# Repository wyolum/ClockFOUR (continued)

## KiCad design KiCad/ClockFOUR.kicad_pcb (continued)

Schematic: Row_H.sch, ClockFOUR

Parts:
C110, C111, C112, C113, C114, C115, C116, C117, C118, C119, C120, C121, C122, C123: 100n; c_0805
LED99, LED100, LED101, LED102, LED103, LED104, LED105, LED106, LED107, LED108, LED109, LED110, LED111, LED112: WS2812B

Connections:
5V: C110.2, C111.2, C112.2, C113.2, C114.2, C115.2, C116.2, C117.2, C118.2, C119.2, C120.2, C121.2, C122.2, C123.2, LED99.1 (VDD), LED100.1 (VDD), LED101.1 (VDD), LED102.1 (VDD), LED103.1 (VDD), LED104.1 (VDD), LED105.1 (VDD), LED106.1 (VDD), LED107.1 (VDD), LED108.1 (VDD), LED109.1 (VDD), LED110.1 (VDD), LED111.1 (VDD), LED112.1 (VDD); also elsewhere on the board
/Row_H/DI_H: LED99.4 (DI); also elsewhere on the board
/Row_I/DI_I: LED112.2 (DO); also elsewhere on the board
GND: C110.1, C111.1, C112.1, C113.1, C114.1, C115.1, C116.1, C117.1, C118.1, C119.1, C120.1, C121.1, C122.1, C123.1, LED99.3 (VSS), LED100.3 (VSS), LED101.3 (VSS), LED102.3 (VSS), LED103.3 (VSS), LED104.3 (VSS), LED105.3 (VSS), LED106.3 (VSS), LED107.3 (VSS), LED108.3 (VSS), LED109.3 (VSS), LED110.3 (VSS), LED111.3 (VSS), LED112.3 (VSS); also elsewhere on the board
unnamed: LED100.2 (DO), LED101.4 (DI)
unnamed: LED99.2 (DO), LED100.4 (DI)
unnamed: LED101.2 (DO), LED102.4 (DI)
unnamed: LED102.2 (DO), LED103.4 (DI)
unnamed: LED103.2 (DO), LED104.4 (DI)
unnamed: LED104.2 (DO), LED105.4 (DI)
unnamed: LED105.2 (DO), LED106.4 (DI)
unnamed: LED106.2 (DO), LED107.4 (DI)
unnamed: LED107.2 (DO), LED108.4 (DI)
unnamed: LED108.2 (DO), LED109.4 (DI)
unnamed: LED109.2 (DO), LED110.4 (DI)
unnamed: LED110.2 (DO), LED111.4 (DI)
unnamed: LED111.2 (DO), LED112.4 (DI)

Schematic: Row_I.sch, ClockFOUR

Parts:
C124, C125, C126, C127, C128, C129, C130, C131, C132, C133, C134, C135, C136, C137: 100n; c_0805
LED113, LED114, LED115, LED116, LED117, LED118, LED119, LED120, LED121, LED122, LED123, LED124, LED125, LED126: WS2812B

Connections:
5V: C124.2, C125.2, C126.2, C127.2, C128.2, C129.2, C130.2, C131.2, C132.2, C133.2, C134.2, C135.2, C136.2, C137.2, LED113.1 (VDD), LED114.1 (VDD), LED115.1 (VDD), LED116.1 (VDD), LED117.1 (VDD), LED118.1 (VDD), LED119.1 (VDD), LED120.1 (VDD), LED121.1 (VDD), LED122.1 (VDD), LED123.1 (VDD), LED124.1 (VDD), LED125.1 (VDD), LED126.1 (VDD); also elsewhere on the board
/Row_I/DI_I: LED113.4 (DI); also elsewhere on the board
/Row_J/DI_J: LED126.2 (DO); also elsewhere on the board
GND: C124.1, C125.1, C126.1, C127.1, C128.1, C129.1, C130.1, C131.1, C132.1, C133.1, C134.1, C135.1, C136.1, C137.1, LED113.3 (VSS), LED114.3 (VSS), LED115.3 (VSS), LED116.3 (VSS), LED117.3 (VSS), LED118.3 (VSS), LED119.3 (VSS), LED120.3 (VSS), LED121.3 (VSS), LED122.3 (VSS), LED123.3 (VSS), LED124.3 (VSS), LED125.3 (VSS), LED126.3 (VSS); also elsewhere on the board
unnamed: LED113.2 (DO), LED114.4 (DI)
unnamed: LED114.2 (DO), LED115.4 (DI)
unnamed: LED115.2 (DO), LED116.4 (DI)
unnamed: LED116.2 (DO), LED117.4 (DI)
unnamed: LED117.2 (DO), LED118.4 (DI)
unnamed: LED118.2 (DO), LED119.4 (DI)
unnamed: LED119.2 (DO), LED120.4 (DI)
unnamed: LED120.2 (DO), LED121.4 (DI)
unnamed: LED121.2 (DO), LED122.4 (DI)
unnamed: LED122.2 (DO), LED123.4 (DI)
unnamed: LED123.2 (DO), LED124.4 (DI)
unnamed: LED124.2 (DO), LED125.4 (DI)
unnamed: LED125.2 (DO), LED126.4 (DI)

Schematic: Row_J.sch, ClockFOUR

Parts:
C138, C139, C140, C141, C142, C143, C144, C145, C146, C147, C148, C149, C150, C151: 100n; c_0805
LED127, LED128, LED129, LED130, LED131, LED132, LED133, LED134, LED135, LED136, LED137, LED138, LED139, LED140: WS2812B; RGB_WS2811B

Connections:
5V: C138.2, C139.2, C140.2, C141.2, C142.2, C143.2, C144.2, C145.2, C146.2, C147.2, C148.2, C149.2, C150.2, C151.2, LED127.1 (VDD), LED128.1 (VDD), LED129.1 (VDD), LED130.1 (VDD), LED131.1 (VDD), LED132.1 (VDD), LED133.1 (VDD), LED134.1 (VDD), LED135.1 (VDD), LED136.1 (VDD), LED137.1 (VDD), LED138.1 (VDD), LED139.1 (VDD), LED140.1 (VDD); also elsewhere on the board
/Row_J/DI_J: LED127.4 (DI); also elsewhere on the board
/Row_K/DI_K: LED140.2 (DO); also elsewhere on the board
GND: C138.1, C139.1, C140.1, C141.1, C142.1, C143.1, C144.1, C145.1, C146.1, C147.1, C148.1, C149.1, C150.1, C151.1, LED127.3 (VSS), LED128.3 (VSS), LED129.3 (VSS), LED130.3 (VSS), LED131.3 (VSS), LED132.3 (VSS), LED133.3 (VSS), LED134.3 (VSS), LED135.3 (VSS), LED136.3 (VSS), LED137.3 (VSS), LED138.3 (VSS), LED139.3 (VSS), LED140.3 (VSS); also elsewhere on the board
unnamed: LED127.2 (DO), LED128.4 (DI)
unnamed: LED128.2 (DO), LED129.4 (DI)
unnamed: LED129.2 (DO), LED130.4 (DI)
unnamed: LED130.2 (DO), LED131.4 (DI)
unnamed: LED131.2 (DO), LED132.4 (DI)
unnamed: LED132.2 (DO), LED133.4 (DI)
unnamed: LED133.2 (DO), LED134.4 (DI)
unnamed: LED134.2 (DO), LED135.4 (DI)
unnamed: LED135.2 (DO), LED136.4 (DI)
unnamed: LED136.2 (DO), LED137.4 (DI)
unnamed: LED137.2 (DO), LED138.4 (DI)
unnamed: LED138.2 (DO), LED139.4 (DI)
unnamed: LED139.2 (DO), LED140.4 (DI)

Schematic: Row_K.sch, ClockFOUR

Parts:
C152, C153, C154, C155, C156, C157, C158, C159, C160, C161, C162, C163, C164, C165: 100n; c_0805
LED141, LED142, LED143, LED144, LED145, LED146, LED147, LED148, LED149, LED150, LED151, LED152, LED153, LED154: WS2812B

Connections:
5V: C152.2, C153.2, C154.2, C155.2, C156.2, C157.2, C158.2, C159.2, C160.2, C161.2, C162.2, C163.2, C164.2, C165.2, LED141.1 (VDD), LED142.1 (VDD), LED143.1 (VDD), LED144.1 (VDD), LED145.1 (VDD), LED146.1 (VDD), LED147.1 (VDD), LED148.1 (VDD), LED149.1 (VDD), LED150.1 (VDD), LED151.1 (VDD), LED152.1 (VDD), LED153.1 (VDD), LED154.1 (VDD); also elsewhere on the board
/Row_K/DI_K: LED141.4 (DI); also elsewhere on the board
/Row_L/DI_L: LED154.2 (DO); also elsewhere on the board
GND: C152.1, C153.1, C154.1, C155.1, C156.1, C157.1, C158.1, C159.1, C160.1, C161.1, C162.1, C163.1, C164.1, C165.1, LED141.3 (VSS), LED142.3 (VSS), LED143.3 (VSS), LED144.3 (VSS), LED145.3 (VSS), LED146.3 (VSS), LED147.3 (VSS), LED148.3 (VSS), LED149.3 (VSS), LED150.3 (VSS), LED151.3 (VSS), LED152.3 (VSS), LED153.3 (VSS), LED154.3 (VSS); also elsewhere on the board
unnamed: LED141.2 (DO), LED142.4 (DI)
unnamed: LED142.2 (DO), LED143.4 (DI)
unnamed: LED143.2 (DO), LED144.4 (DI)
unnamed: LED144.2 (DO), LED145.4 (DI)
unnamed: LED145.2 (DO), LED146.4 (DI)
unnamed: LED146.2 (DO), LED147.4 (DI)
unnamed: LED147.2 (DO), LED148.4 (DI)
unnamed: LED148.2 (DO), LED149.4 (DI)
unnamed: LED149.2 (DO), LED150.4 (DI)
unnamed: LED150.2 (DO), LED151.4 (DI)
unnamed: LED151.2 (DO), LED152.4 (DI)
unnamed: LED152.2 (DO), LED153.4 (DI)
unnamed: LED153.2 (DO), LED154.4 (DI)

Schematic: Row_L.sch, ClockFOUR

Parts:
C166, C167, C168, C169, C170, C171, C172, C173, C174, C175, C176, C177, C178, C179: 100n; c_0805
LED155, LED156, LED157, LED158, LED159, LED160, LED161, LED162, LED163, LED164, LED165, LED166, LED167, LED168: WS2812B

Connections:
5V: C166.2, C167.2, C168.2, C169.2, C170.2, C171.2, C172.2, C173.2, C174.2, C175.2, C176.2, C177.2, C178.2, C179.2, LED155.1 (VDD), LED156.1 (VDD), LED157.1 (VDD), LED158.1 (VDD), LED159.1 (VDD), LED160.1 (VDD), LED161.1 (VDD), LED162.1 (VDD), LED163.1 (VDD), LED164.1 (VDD), LED165.1 (VDD), LED166.1 (VDD), LED167.1 (VDD), LED168.1 (VDD); also elsewhere on the board
/Row_L/DI_L: LED155.4 (DI); also elsewhere on the board
/Row_M/DI_M: LED168.2 (DO); also elsewhere on the board
GND: C166.1, C167.1, C168.1, C169.1, C170.1, C171.1, C172.1, C173.1, C174.1, C175.1, C176.1, C177.1, C178.1, C179.1, LED155.3 (VSS), LED156.3 (VSS), LED157.3 (VSS), LED158.3 (VSS), LED159.3 (VSS), LED160.3 (VSS), LED161.3 (VSS), LED162.3 (VSS), LED163.3 (VSS), LED164.3 (VSS), LED165.3 (VSS), LED166.3 (VSS), LED167.3 (VSS), LED168.3 (VSS); also elsewhere on the board
unnamed: LED155.2 (DO), LED156.4 (DI)
unnamed: LED156.2 (DO), LED157.4 (DI)
unnamed: LED157.2 (DO), LED158.4 (DI)
unnamed: LED158.2 (DO), LED159.4 (DI)
unnamed: LED159.2 (DO), LED160.4 (DI)
unnamed: LED160.2 (DO), LED161.4 (DI)
unnamed: LED161.2 (DO), LED162.4 (DI)
unnamed: LED162.2 (DO), LED163.4 (DI)
unnamed: LED163.2 (DO), LED164.4 (DI)
unnamed: LED164.2 (DO), LED165.4 (DI)
unnamed: LED165.2 (DO), LED166.4 (DI)
unnamed: LED166.2 (DO), LED167.4 (DI)
unnamed: LED167.2 (DO), LED168.4 (DI)

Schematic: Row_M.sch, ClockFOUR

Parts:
C180, C181, C182, C183, C184, C185, C186, C187, C188, C189, C190, C191, C192, C193: 100n; c_0805
LED169, LED170, LED171, LED172, LED173, LED174, LED175, LED176, LED177, LED178, LED179, LED180, LED181, LED182: WS2812B; RGB_WS2811B

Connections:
5V: C180.2, C181.2, C182.2, C183.2, C184.2, C185.2, C186.2, C187.2, C188.2, C189.2, C190.2, C191.2, C192.2, C193.2, LED169.1 (VDD), LED170.1 (VDD), LED171.1 (VDD), LED172.1 (VDD), LED173.1 (VDD), LED174.1 (VDD), LED175.1 (VDD), LED176.1 (VDD), LED177.1 (VDD), LED178.1 (VDD), LED179.1 (VDD), LED180.1 (VDD), LED181.1 (VDD), LED182.1 (VDD); also elsewhere on the board
/Row_M/DI_M: LED169.4 (DI); also elsewhere on the board
/Row_M/DO_M: LED182.2 (DO)
GND: C180.1, C181.1, C182.1, C183.1, C184.1, C185.1, C186.1, C187.1, C188.1, C189.1, C190.1, C191.1, C192.1, C193.1, LED169.3 (VSS), LED170.3 (VSS), LED171.3 (VSS), LED172.3 (VSS), LED173.3 (VSS), LED174.3 (VSS), LED175.3 (VSS), LED176.3 (VSS), LED177.3 (VSS), LED178.3 (VSS), LED179.3 (VSS), LED180.3 (VSS), LED181.3 (VSS), LED182.3 (VSS); also elsewhere on the board
unnamed: LED169.2 (DO), LED170.4 (DI)
unnamed: LED170.2 (DO), LED171.4 (DI)
unnamed: LED171.2 (DO), LED172.4 (DI)
unnamed: LED172.2 (DO), LED173.4 (DI)
unnamed: LED173.2 (DO), LED174.4 (DI)
unnamed: LED174.2 (DO), LED175.4 (DI)
unnamed: LED175.2 (DO), LED176.4 (DI)
unnamed: LED176.2 (DO), LED177.4 (DI)
unnamed: LED177.2 (DO), LED178.4 (DI)
unnamed: LED178.2 (DO), LED179.4 (DI)
unnamed: LED179.2 (DO), LED180.4 (DI)
unnamed: LED180.2 (DO), LED181.4 (DI)
unnamed: LED181.2 (DO), LED182.4 (DI)

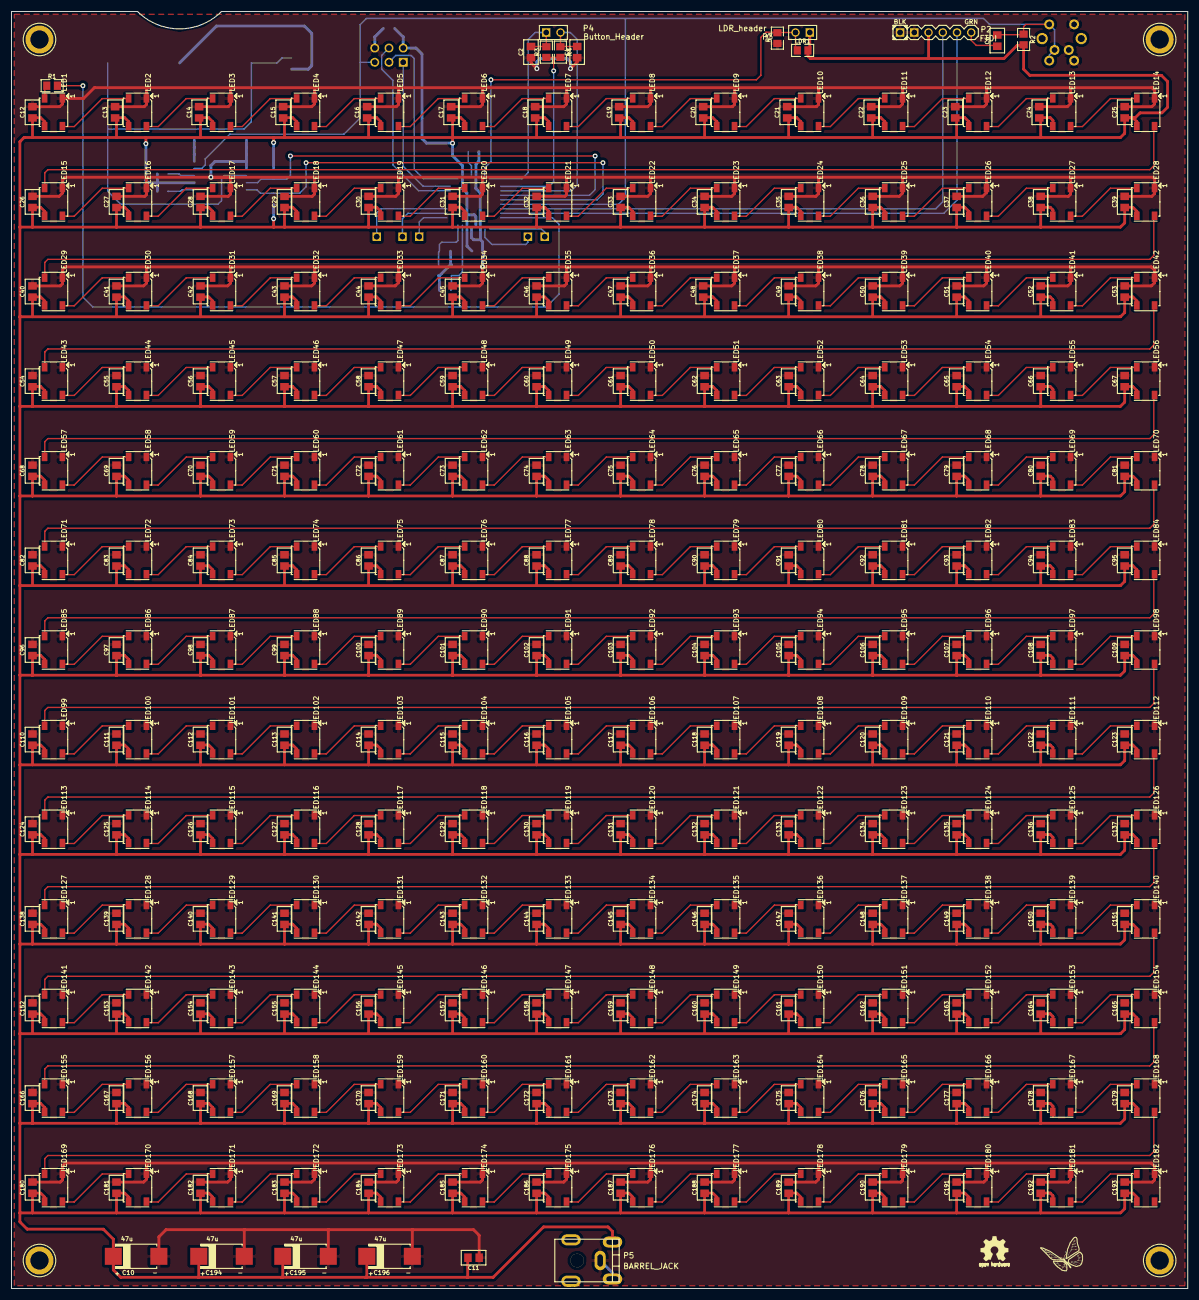
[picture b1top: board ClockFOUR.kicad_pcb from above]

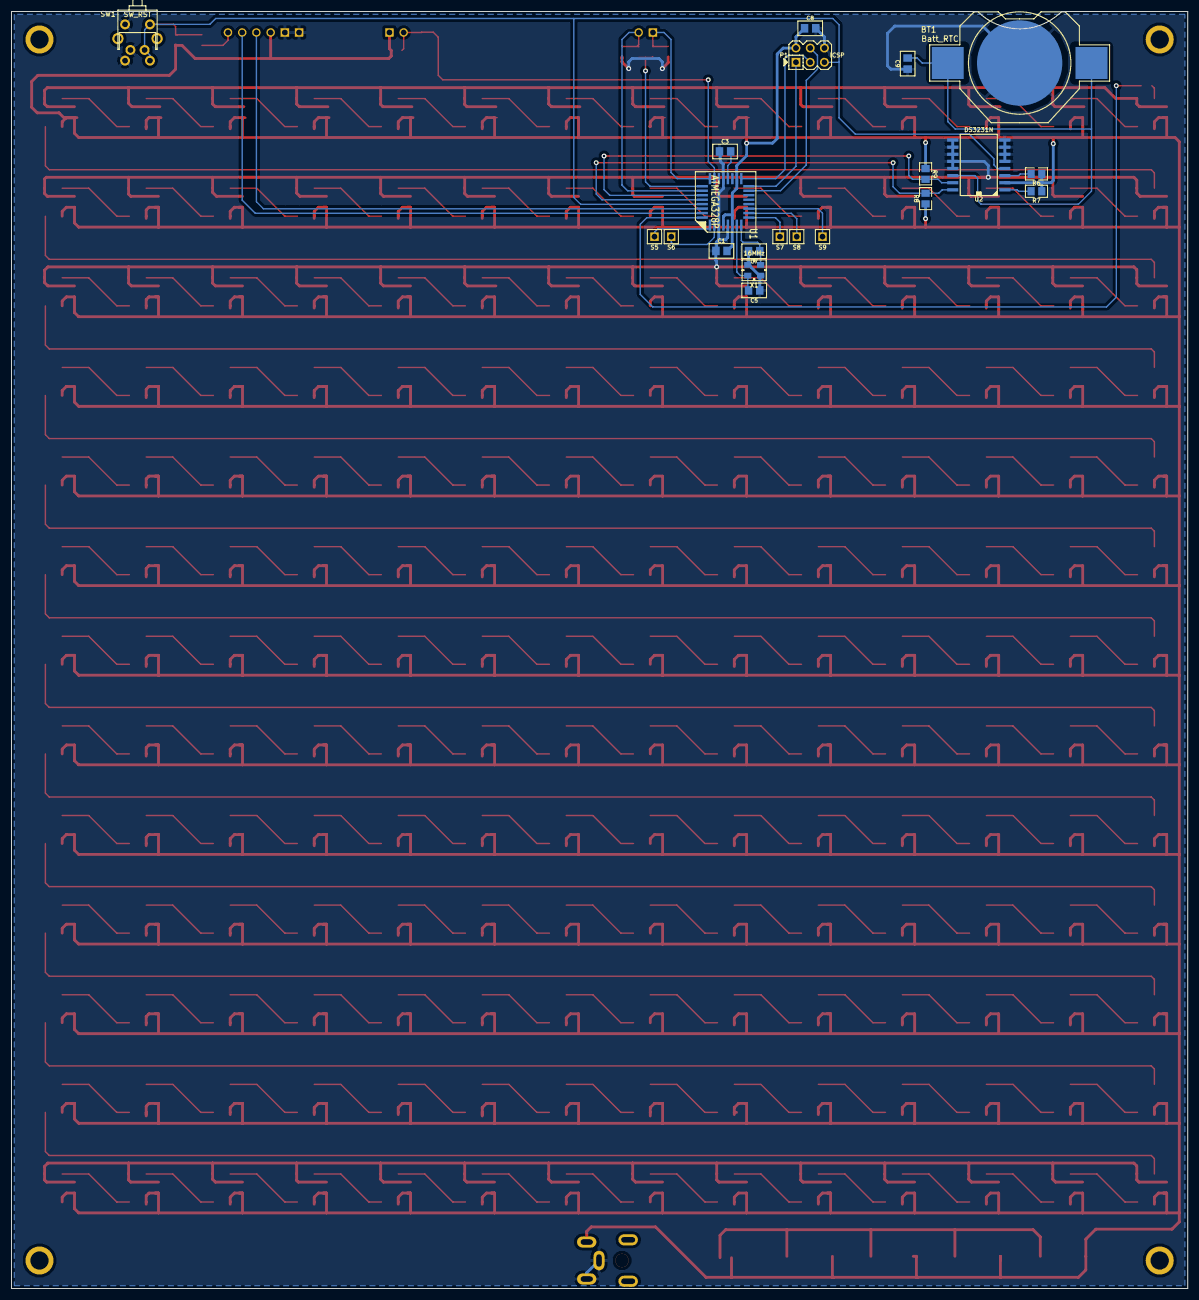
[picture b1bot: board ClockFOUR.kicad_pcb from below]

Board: 2 copper layers, 210.0 x 228.0 mm, 409 parts (21 on the bottom side), 209 nets.

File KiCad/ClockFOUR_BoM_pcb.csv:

"Id";"Designator";"Package";"Quantity";"Designation";"Supplier and ref";
1;"L1";"C4_Pretty:Logo_silk_OSHW_6x6mm";1;"OSHW";;;
2;"L2";"C4_Pretty:Logo-WL3";1;"Wyolum";;;
3;"R1";"C4_Pretty:r_0805";1;"500R";;;
4;"S4,S3,S2,S1";"C4_Pretty:Screw_3mm";4;"CONN_1";;;
5;"S9,S8,S7,S6,S5";"C4_Pretty:BreakOutPad";5;"CONN_1";;;
6;"P5";"C4_Pretty:JACK_PJ-047a";1;"BARREL_JACK";;;
7;"S13,S12,S11,S10";"C4_Pretty:Screw_2mm";4;"CONN_1";;;
8;"BT1";"C4_Pretty:CR2032_SMD";1;"Batt_RTC";;;
9;"U2";"C4_Pretty:DS3231";1;"DS3231N";;;
10;"R7,R6,R5,R2";"C4_Pretty:r_0805";4;"10K";;;
11;"R9,R8";"C4_Pretty:r_0805";2;"4K7";;;
12;"X1";"C4_Pretty:Xtal_SMD3";1;"16MHz";;;
13;"U1";"C4_Pretty:TQFP32";1;"ATMEGA328P";;;
14;"P1";"C4_Pretty:ISP";1;"ICSP";;;
15;"R3,R4";"C4_Pretty:r_0805";2;"1M";;;
16;"P4";"C4_Pretty:SIL-2";1;"Button_Header";;;
17;"P3";"C4_Pretty:SIL-2";1;"LDR_header";;;
18;"LDR1";"C4_Pretty:r_0805";1;"LDR";;;
19;"SW1";"C4_Pretty:SW_PB_V_H";1;"SW_RST";;;
20;"C10,C196,C195,C194";"C4_Pretty:c_2917";4;"47u";;;
21;"C6,C8,C9,C3,C1,C11,C197,C198";"C4_Pretty:c_0805";8;"100n";;;
22;"C4,C2";"C4_Pretty:c_0805";2;"100p";;;
23;"C7,C5";"C4_Pretty:c_0805";2;"22p";;;
24;"C193,C192,C191,C190,C189,C188,C187,C186,C185,C184,C183,C182,C181,C180,C179,C178,C177,C176,C175,C174,C173,C172,C171,C170,C169,C168,C167,C166,C165,C164,C163,C162,C161,C160,C159,C158,C157,C156,C155,C154,C153,C152,C151,C150,C149,C148,C147,C146,C145,C144,C143,C142,C141,C140,C139,C138,C137,C136,C135,C134,C133,C132,C131,C130,C129,C128,C127,C126,C125,C124,C123,C122,C121,C120,C119,C118,C117,C116,C115,C114,C113,C112,C111,C110,C109,C108,C107,C106,C105,C104,C103,C102,C101,C100,C99,C98,C97,C96,C95,C94,C93,C92,C91,C90,C89,C88,C87,C86,C85,C84,C83,C82,C81,C80,C79,C78,C77,C76,C75,C74,C73,C72,C71,C70,C69,C68,C67,C66,C65,C64,C63,C62,C61,C60,C59,C58,C57,C56,C55,C54,C53,C52,C51,C50,C49,C48,C47,C46,C45,C44,C43,C42,C41,C40,C39,C38,C37,C36,C35,C34,C33,C32,C31,C30,C29,C28,C27,C26,C25,C24,C23,C22,C21,C20,C19,C18,C17,C16,C15,C14,C13,C12";"C4_Pretty:c_0805_led";182;"100n";;;
25;"LED20,LED182,LED181,LED180,LED179,LED178,LED177,LED176,LED175,LED174,LED173,LED172,LED171,LED170,LED169,LED168,LED167,LED166,LED165,LED164,LED163,LED162,LED161,LED160,LED159,LED158,LED157,LED156,LED155,LED154,LED153,LED152,LED151,LED150,LED149,LED148,LED147,LED146,LED145,LED144,LED143,LED142,LED141,LED140,LED139,LED138,LED137,LED136,LED135,LED134,LED133,LED132,LED131,LED130,LED129,LED128,LED127,LED126,LED125,LED124,LED123,LED122,LED121,LED120,LED119,LED118,LED117,LED116,LED115,LED114,LED113,LED112,LED111,LED110,LED109,LED108,LED107,LED106,LED105,LED104,LED103,LED102,LED101,LED100,LED99,LED98,LED97,LED96,LED95,LED94,LED93,LED92,LED91,LED90,LED89,LED88,LED87,LED86,LED85,LED84,LED83,LED82,LED81,LED80,LED79,LED78,LED77,LED76,LED75,LED74,LED73,LED72,LED71,LED70,LED69,LED68,LED67,LED66,LED65,LED64,LED63,LED62,LED61,LED60,LED59,LED58,LED57,LED56,LED55,LED54,LED53,LED52,LED51,LED50,LED49,LED48,LED47,LED46,LED45,LED44,LED43,LED42,LED41,LED40,LED39,LED38,LED37,LED36,LED35,LED34,LED33,LED32,LED31,LED30,LED29,LED28,LED27,LED26,LED25,LED24,LED23,LED22,LED21,LED19,LED18,LED17,LED16,LED15,LED14,LED13,LED12,LED11,LED10,LED9,LED8,LED7,LED6,LED5,LED4,LED3,LED2,LED1";"C4_Pretty:RGB_WS2811B";182;"WS2812B";;;
26;"P2";"C4_Pretty:Header_FTDI";1;"FTDI";;;
27;"G1";"C4_Pretty:Logo-WL3";1;"Logo-WL3";;;
28;"P6";"C4_Pretty:r_0805";1;"5VEN_L";;;
29;"P8";"C4_Pretty:r_0805";1;"5VEN_R";;;
30;"P9";"C4_Pretty:STACK-R";1;"I2C_R";;;
31;"P7";"C4_Pretty:STACK-L";1;"I2C_L";;;

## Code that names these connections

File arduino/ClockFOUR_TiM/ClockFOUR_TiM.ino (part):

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#endif

/************* Pin settings *************/
#define MATRIX_PIN			5
#define BUTTON_L			6
#define BUTTON_R			A0
#define CAP_SENSE			A1
#define LDR_PIN				A7


/************* Some display settings *************/
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	Wire.begin();

	// Initialise the board inputs and outputs
	pinMode(MATRIX_PIN, OUTPUT);   // declare the ledPin as an OUTPUT:
	pinMode(LDR_PIN, INPUT);       // declare the LDRPin as an INPUT:
	
	// Initialise the display
	disp_init();
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
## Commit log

2014-07-10 compliles... not functional yet
2014-07-30 Added firmware quick reference guide
    Description of how the modes will work with only two buttons
2014-08-13 Added ClockTiM, the world clock with GPS support
2014-08-14 Got key presses working with detection of long key presses
2014-08-16 Fixed the getKeys() function so it returns recently pressed keys, long pressed keys and also has repeat after long-press functionality
2014-08-16 Separated out parts of code into their own files
2014-08-16 Clock_TiM Baffles and Facplate
    Created baffles and faceplate generation code
2014-08-16 Finally got push-button code clean and working. Implemented routines for settings configuration.
2014-08-20 Created faceplate and baffles for 30x30 clock
2014-08-21 New test setup, added LDR and Pot
    KnobPin = A6;
    LDRPin = A7;
    stripPin = 5;
    Button1 = 6;
    Button2 = 7;
2014-08-22 Created language files for Clock_TiM and Clock_30
2014-08-22 Directory cleanup
2014-08-22 RTC functionality added
2014-08-22 Minor mods
2014-08-22 Seconds displayed + updates to library
    NeoMatrix + NeoPixel instances running at the same time
2014-08-22 Updated Clock_30 baffles
    Enabled vertical baffles to "jump_strips" and lay flat over LED strips
2014-08-25 Added Cap sense switches
    Replaced buttons with touch sensors
2014-08-25 Correctly displays the time!
2014-08-25 All colour modes working
2014-08-25 Added matrix code
2014-08-26 Added temperature display via RTC
2014-08-26 Changed orientation of the display and cleaned up some display functions
2014-08-27 Moved display code to separate file, colour modes
2014-08-27 Added code to show the time
2014-08-27 Nightly update
2014-08-28 Added modes description to docs
2014-08-28 Modified OneCapSensor so that it works with the capacitive buttons. Used this new library to replce the getKeys() function. Separated the settings of the LEDs and the displaying of them; two function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
2014-08-28 Added long press of the left button to quit current config mode
2014-08-28 Modes description updated
2014-08-28 Added some comments to the queue code
2014-08-29 Added modes??
2014-08-29 Needs debugging
    Seems buttons are detected despite no actual keypresses.
2014-08-30 Wrote ButtonTest program to test input keys
    Input is not working as expected.
2014-08-30 C3jr style menus implemented
    Hangs just after first loop through main program.
2014-08-31 Copied code to ClockTiM_old
2014-08-31 Created a funcitonal clock (with inaccurate timing). Makes use of display and colour modes.
2014-09-01 Moved to ClockFOUR_TiM folder
2014-09-01 Implemented display_refresh with multiple colour fades, animations
2014-09-02 Temp working from RTC
    Displays deg C and deg F according to settings
2014-09-04 Added scrolling text
    at startup and during config mode
2014-09-04 RTC?
    Poor attempt to add RTC code. Not working.
2014-09-05 RTC works correctly
2014-09-06 A bit of beautifying and making the code clearer: each pointer (except for some arrays) now have the prefix 'p_'
2014-09-07 Major change to the way PixelStates works. It is now parametrisable like NeoMatrix, and methods have been implemented to write to a certain LED, and to read LEDs directly for the NeoPixel strip.
2014-09-07 Created a tool called bmp2h that converts bitmap files into structs to be used in a C program. Implemented a function in PixelStates to load bmp generated in this way.
2014-09-08 Created the waitDelayOrButton() function that causes a delay that can be interrupted by a button press
2014-09-08 temp
2014-09-08 Merge remote-tracking branch 'origin/master'
    Conflicts:
    arduino/ClockFOUR_TiM/ClockFOUR_TiM.ino
2014-09-08 Re-added the delay/button press function
2014-09-08 Added Min and Temp bitmaps
2014-09-08 Added degree symbol
2014-09-08 Added "minute slider" under seconds display
2014-09-09 Removed minute slider, left code in as an option
2014-09-12 ClockFOUR_30 is alive!
2014-09-14 Changed the OneCapSense lib to allow for click, long press and double long press detection. Upon left long press colour mode can be selected, whereas after long right press the config mode is entered.
2014-09-14 Updated changes to Clock30
2014-09-14 And forgot the update bitmap.h file
2014-09-15 Clock_30 updates
2014-09-19 Minor changes to Clock_Tim, Fast LED library
2014-09-19 Added a few FastLED examples
2014-09-19 Reduced the number of colour modes and cleaned up the code around that. The colour wheel can now be used to pick a solid colour.
2014-09-23 Changed PixelStates a bit to allow for colour bitmaps. Implemented colour bitmaps. Added a repeatDelay variable to the changeSettings function. Changed all constant array declarations so that they ar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
2014-09-26 Kicad schematic started
2014-09-29 Schematic updated
2014-10-01 Schematic updated, board started
2014-10-02 Board layout updated
2014-10-03 Board layout updated
    Matrix placed and wired. Added RTC.
2014-10-06 Layout updated
2014-10-06 Layout updated
    added 4x caps on power input. Replace with single larger cap??
2014-10-06 Completed Layout for review
    Version alpha 0.1
2014-10-06 Commit w/ libs
2014-10-06 Another try - with .lib
2014-10-07 Layout changes
    + increased size of 5V traces
    + board notch around RTC battery
    + added breakout pins
2014-10-08 Layout updated
    Fixed thin trace clearance error on ucontroller.
2014-10-08 Added Gerber files
2014-10-08 Anool's version of pcb saved as ClockFOUR_anool.kicad_pcb
2014-10-09 Connector nudged, sent to Seed for quotation
2014-10-09 New power jack added
2014-10-09 PCB layout, work in progress
2014-10-10 C4 PCB layout complete. Added Gerbers
2014-10-10 C4 PCB layout complete. BoM in progress
2014-10-10 C4 board layout complete. Gerbers and BoM ready
2014-10-11 Updated faceplate and baffles to match PCB
2014-10-11 C4 added spare buttons, SMD push buttons, I2C address ports etc
2014-10-12 Added pixel fading over time.
2014-10-13 C4 added NiL header
2014-10-14 C4 some minor mods to PCB layout
2014-10-16 Added smooth fading. Get input function now has a timeout. Entering config mode does not block when the button is pressed. 'Set' is now displayed in config mode.
2014-10-16 Nil header, added SMD switches, BoM modified
2014-10-17 NiL connector moved to lower left corner of board
2014-10-20 C4 final prototype Gerbers ready
2014-10-26 Moved changes from ClockFOUR_TiM to ClockFOUR_30
2014-10-26 Removed secondary colour buffer to save RAM. Random colours are now created predicatably based random 32-bit seed.
2014-10-26 Made the hasing function more efficient.
2014-10-26 Updated changes to ClockFOUR_30
2014-10-26 Clock_30: centred letters, fixed text wrap
2014-12-04 Created folder for ClockFOUR_v1 prototype boards
    Code location for v1 prototype boards
2014-12-05 Minor tweaks
2014-12-06 New 14x13 bitmaps
    Bitmaps for new display
2014-12-08 Linear HSV style Rainbow color wheel
    Added lookup table for equal rainbow colour spacing.
2014-12-08 Slow fade on temp display
2014-12-12 Removed cap sense, added button code
    Works with buttons on the back of the clock
2014-12-12 Removed Temp mode & references to GPS
    Temp mode deleted. All references to GPS removed.
2014-12-12 Deleted temp bitmap
2014-12-13 Added code to change the settings for the logo at the bottom. These colours should also be displayed.
2014-12-17 Physical housing updates
2015-01-05 BoM updated
2015-01-09 working on rev 2 of ClockFOUR
2015-01-21 Schematic Changes
    1. Touch circuitry removed. Pins changed to breakout pins.
    2. "Name in Lights" and NiL changed to "Marquee"
    3. P10 connector - added 4th pin
    1. MARQUEE_DATA (through a 470R resistor)
    2. MARQUEE_SENSE pin pulled high via 10k resistor. When this pin is
    grounded clock knows Marquee is connected
2015-01-22 minor cleanup
2015-01-23 Schematic changes - 3x LDR
    3x LDR's to be placed below LED1, LED14 and LED121.
    Removed external LDR header.
2015-01-26 Updated mechanical design
    Faceplate and baffle generation script updates
    Assembly mock-up drawing updated
2015-01-26 C4 rev2 aka Chronogram, Sch and PCB mods, revised BoM
2015-01-27 Added Fuse/Zener protection, silk legend mods
2015-01-27 Minor board tweaks
    Trying to add a logo to the back of the board
2015-01-28 Assembly C4_v2 folder created
    Assembly BOM updated
    created folder to send Seeed for latest prototype
2015-01-29 Headers moved, Silk Legend update, BoM update, Gerber generated
2015-01-29 Revised backplate
    Added backplate cut out holes and etching
2015-01-29 Revised clock sides, added test plan and instructions
2015-01-29 FINAL CHECK - are we ready to order?
2015-01-30 V2 Files sent to Seeed
2015-01-30 Version 2.1 - sent to Seeed
    Adjusted FTDI cutout hole down 4mm
2015-01-31 Added marquee strip settings and code. UNTESTED.
2015-01-31 Added smarter logic for brightness detection.
2015-01-31 Brightness no longer changes in a linear manner
2015-02-01 Mod brightness code, debug
    Changed Clock4 splash to Chronogram
2015-02-11 added EPS and SVG formats for laster cut parts
2015-04-02 C4_v2 prototype w/ 3x LDR working
    Updated LDR code
    adjusted LDR brightness thresholds
2015-04-03 Got marquee working.
2015-04-05 Setup the clock to use three LDRs.
2015-10-03 added LDR4
2015-10-04 Added a header to every file with license info etc. Brightness can now be automatic, or between 1 and 5, user configurable.
2015-10-05 Added the clock_defines.h file that I forgot in the last commit
2015-10-06 Kicad mods done. Gerbers, PDF ready
2015-10-07 ver 3.0 BoM finalized
2015-10-10 Preparing for final design changes
    Moving files to their new location, minor changes to baffles.
2015-10-12 ClockFOUR ver 3.0 final schematic, layout, gerber plots and BoM for production
2015-10-12 added 3D printable bracket for power socket wall mounting option
2018-07-15 added Gerber ZIP
